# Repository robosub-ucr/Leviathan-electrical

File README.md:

# Electrical
PCB blueprints and other electrical things
PCB Article links: The story of how UCR RoboSub SeaDragon PCB's came to be

Buck Converter PDB Story: https://www.hackster.io/LevithianSub/buck-converter-pdb-9757d3

Arduino Mega Peripheral Board Story: https://www.hackster.io/LevithianSub/arduino-mega-peripheral-board-a77800

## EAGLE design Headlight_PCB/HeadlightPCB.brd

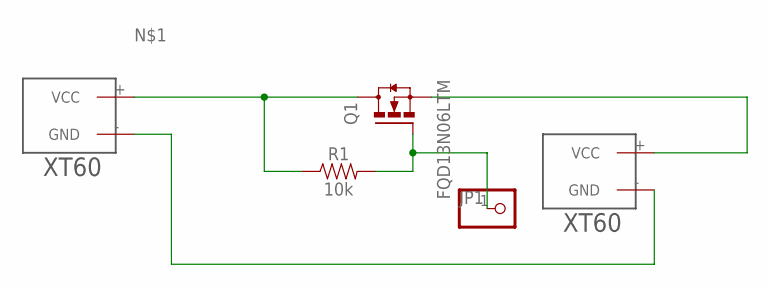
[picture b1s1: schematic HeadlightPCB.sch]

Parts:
JP1: PINHD-1X1; 1X01
Q1: FQD13N06LTM; DPAK4
R1: 10k; 0603
U$2: XT60
VIN: XT60

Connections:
unnamed: Q1.2 (D), Q1.4 (D), R1.1, VIN.+ (VCC)
unnamed: Q1.3 (S), U$2.+ (VCC)
unnamed: U$2.- (GND), VIN.- (GND)
unnamed: JP1.1, Q1.1 (G), R1.2

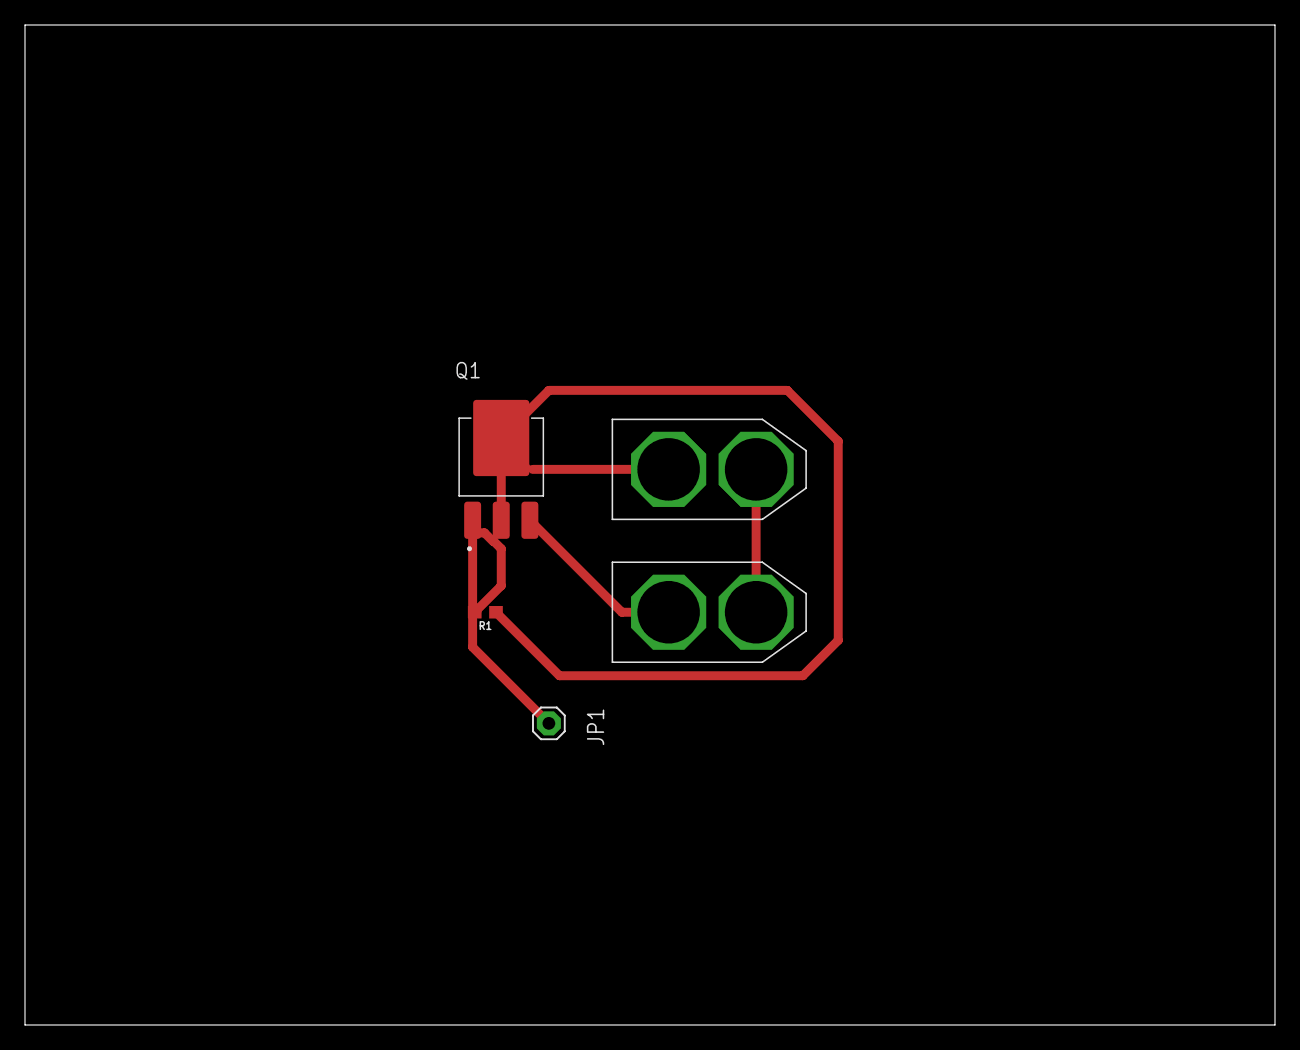
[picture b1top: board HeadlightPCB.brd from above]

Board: 2 copper layers, 100.0 x 80.0 mm, 5 parts (0 on the bottom side), 4 nets.

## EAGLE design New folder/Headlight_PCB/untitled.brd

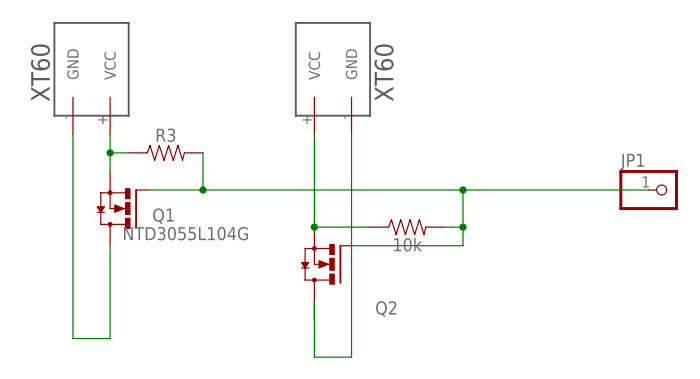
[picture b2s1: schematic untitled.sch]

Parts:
JP1: PINHD-1X1; 1X01
Q1, Q2: NTD3055L104G; DPAK4
R3, R4: 10k; 0402
U$1, U$2: XT60

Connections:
unnamed: Q1.3 (S), R3.1, U$1.+ (VCC)
unnamed: Q1.2 (D), Q1.4 (D), U$1.- (GND)
unnamed: Q2.2 (D), Q2.4 (D), U$2.- (GND)
unnamed: Q2.3 (S), R4.1, U$2.+ (VCC)
unnamed: JP1.1, Q1.1 (G), Q2.1 (G), R3.2, R4.2

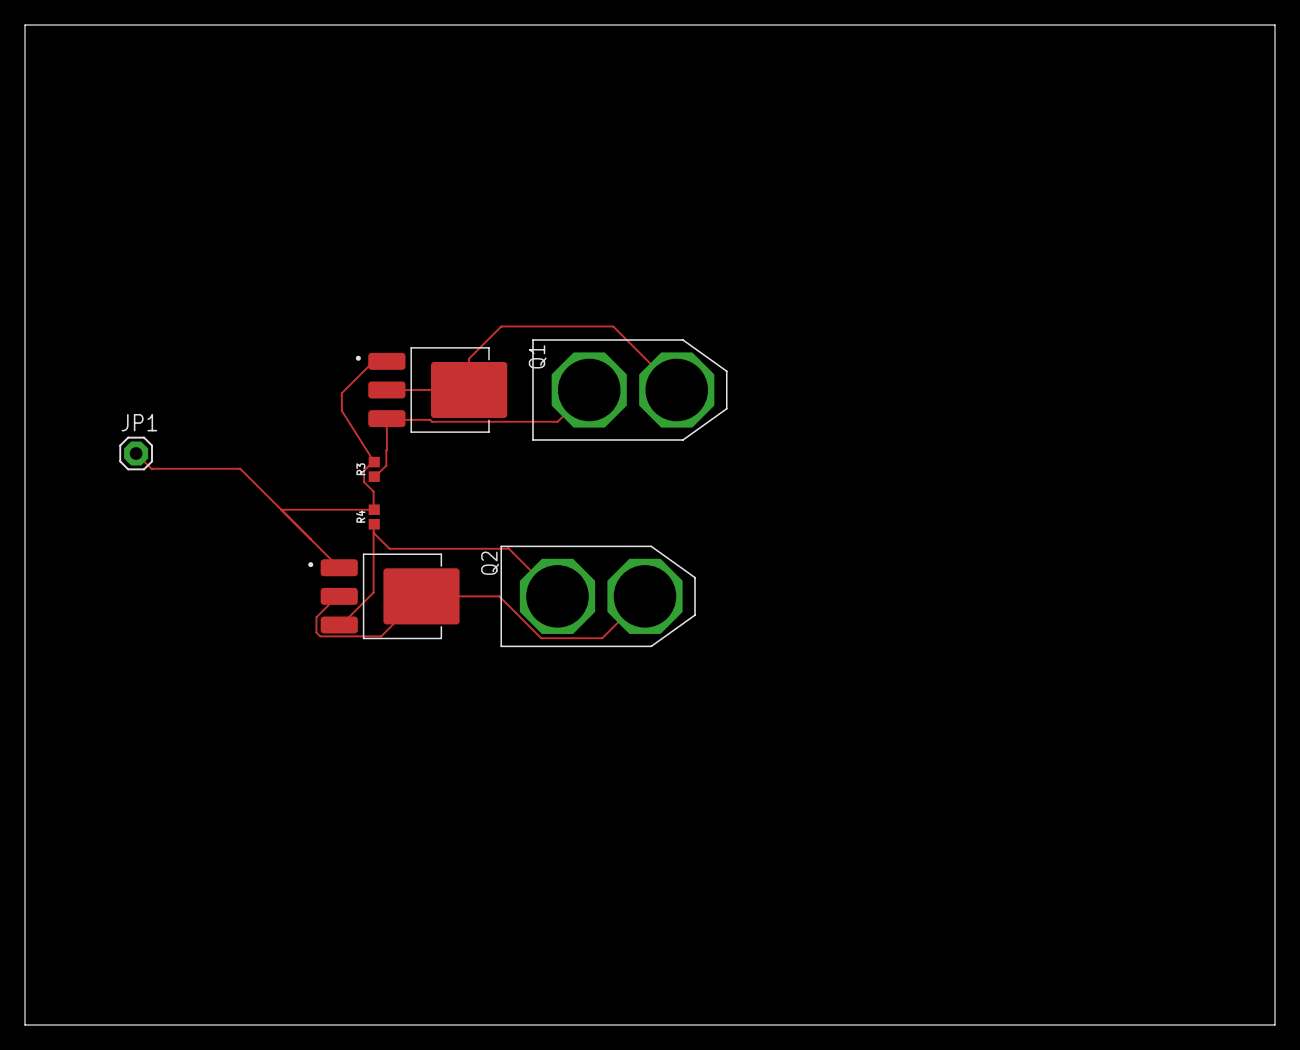
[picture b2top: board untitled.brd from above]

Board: 2 copper layers, 100.0 x 80.0 mm, 7 parts (0 on the bottom side), 5 nets.

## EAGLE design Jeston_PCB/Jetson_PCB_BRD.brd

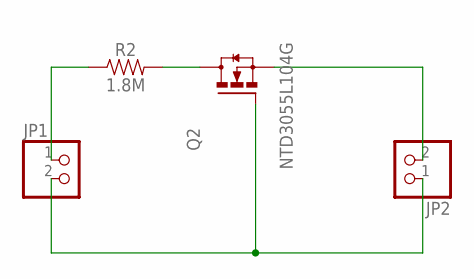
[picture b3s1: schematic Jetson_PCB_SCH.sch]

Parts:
JP1, JP2: PINHD-1X2; 1X02
Q2: NTD3055L104G; DPAK4
R2: 1.8M; 0603

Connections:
unnamed: JP1.2, JP2.1, Q2.1 (G)
unnamed: JP1.1, R2.1
unnamed: Q2.2 (D), Q2.4 (D), R2.2
unnamed: JP2.2, Q2.3 (S)

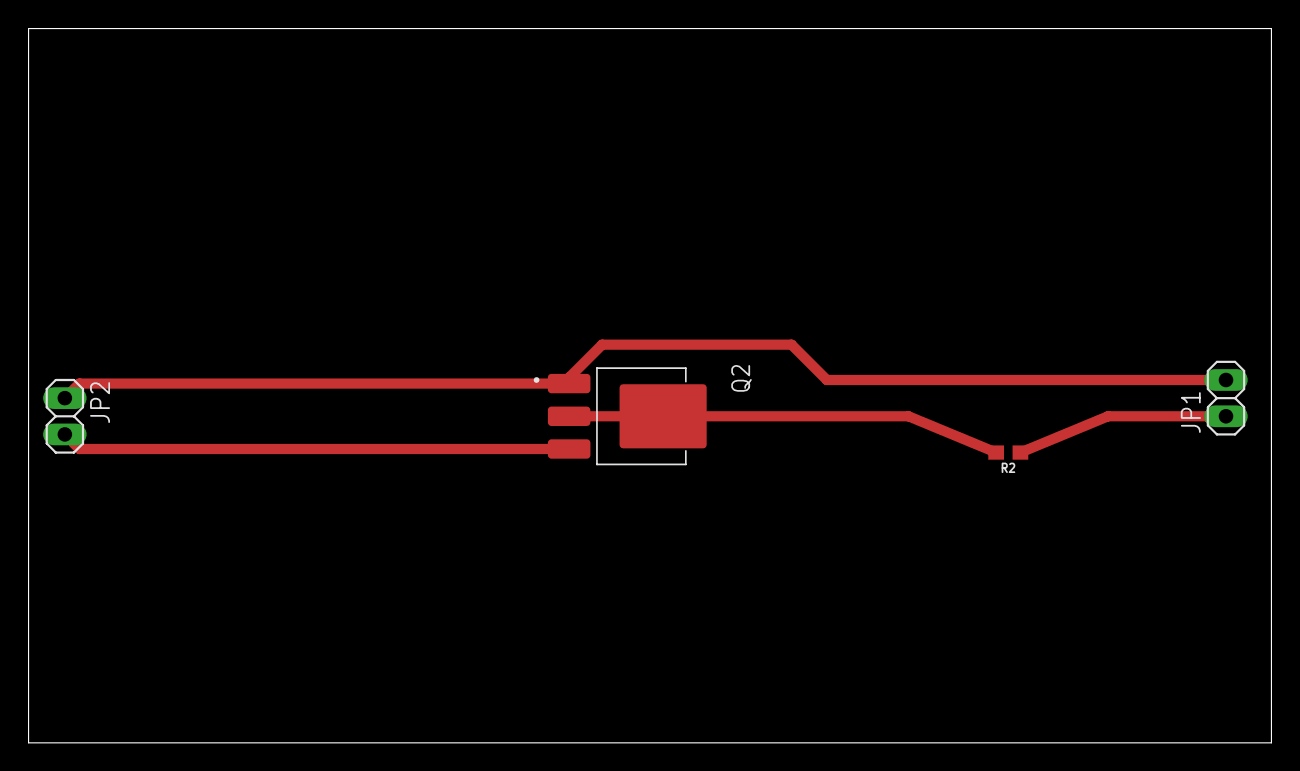
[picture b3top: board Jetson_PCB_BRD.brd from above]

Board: 2 copper layers, 87.0 x 50.0 mm, 4 parts (0 on the bottom side), 4 nets.

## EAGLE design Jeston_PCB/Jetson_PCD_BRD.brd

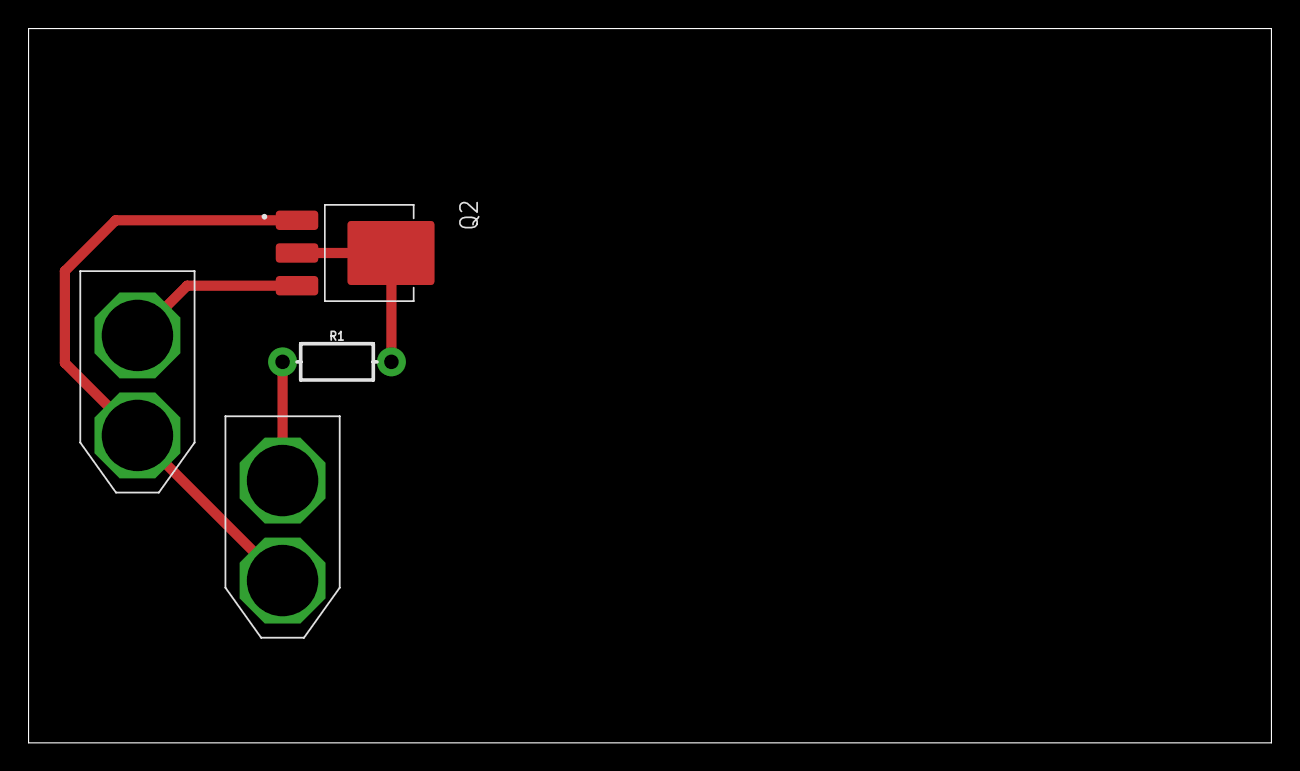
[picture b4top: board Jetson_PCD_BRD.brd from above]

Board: 2 copper layers, 87.0 x 50.0 mm, 4 parts (0 on the bottom side), 4 nets.

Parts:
Q2: NTD3055L104G; DPAK4
R1: AXIAL-0.3-KIT
U$1, U$2: XT60

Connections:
unnamed: Q2.1, U$1.-, U$2.-
unnamed: R1.P$1, U$2.+
unnamed: Q2.2, Q2.4, R1.P$2
unnamed: Q2.3, U$1.+

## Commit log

2019-09-21 New folder
2019-09-21 removed "new folder" used for testing git commands
2019-09-21 uploading first tries at Jetson and Headlights PCBs
2019-09-24 Updating\renaming Headlight_PCB files, adding pngs
2019-09-24 Renaming Jetson_PCB files, added images
2019-10-03 Thruster PDB redesign project for the new sub
2019-10-04 sexample commit
2019-10-04 deleted Ivans files
2019-10-04 example commit
2019-10-04 Added new pcb png
2019-10-04 Merge remote-tracking branch 'origin/Matthew' into Matthew_testing&development
    example 2
2019-10-04 example
2019-10-05 image of thruster PCB
2019-10-05 fixed add 5v source to desgin
2019-10-06 replaced battery port with XT60
2019-10-06 created .gitignore file
2019-10-06 updating README.md
2019-10-07 reorganizing image library
2019-10-08 replacing ports to pins, different resistor footprint
2019-10-19 nothing to see here
2019-10-19 began making pcb board
2019-10-19 teensy.IntLib
2019-10-19 replaced the teensy and moved around componets
2019-10-19 new PCB
2019-10-19 ESC.IntLib
2019-10-26 update- redoing ESC mount source file due to footprint flaw
2019-10-26 updating schematic picture
2019-10-26 changed source file for esc and updating schematic to reflect changes. Also creating new PCB to work with
2019-11-08 Buck Converter, by Roger T
    Buck Conveter schematic needs to be reviewed for connectors to voltage sensor
2019-11-26 task board
2019-11-26 Thruster Board update
2020-01-24 Kevin_Jetson_PCB/
    Kevin Version of the PCB board, and meets specs for jetson, trace: 50mil.

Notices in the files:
parts and their libraries:
SparkFun-Resistors: Licensing: Creative Commons ShareAlike 4.0 International - https://creativecommons.org/licenses/by-sa/4.0
